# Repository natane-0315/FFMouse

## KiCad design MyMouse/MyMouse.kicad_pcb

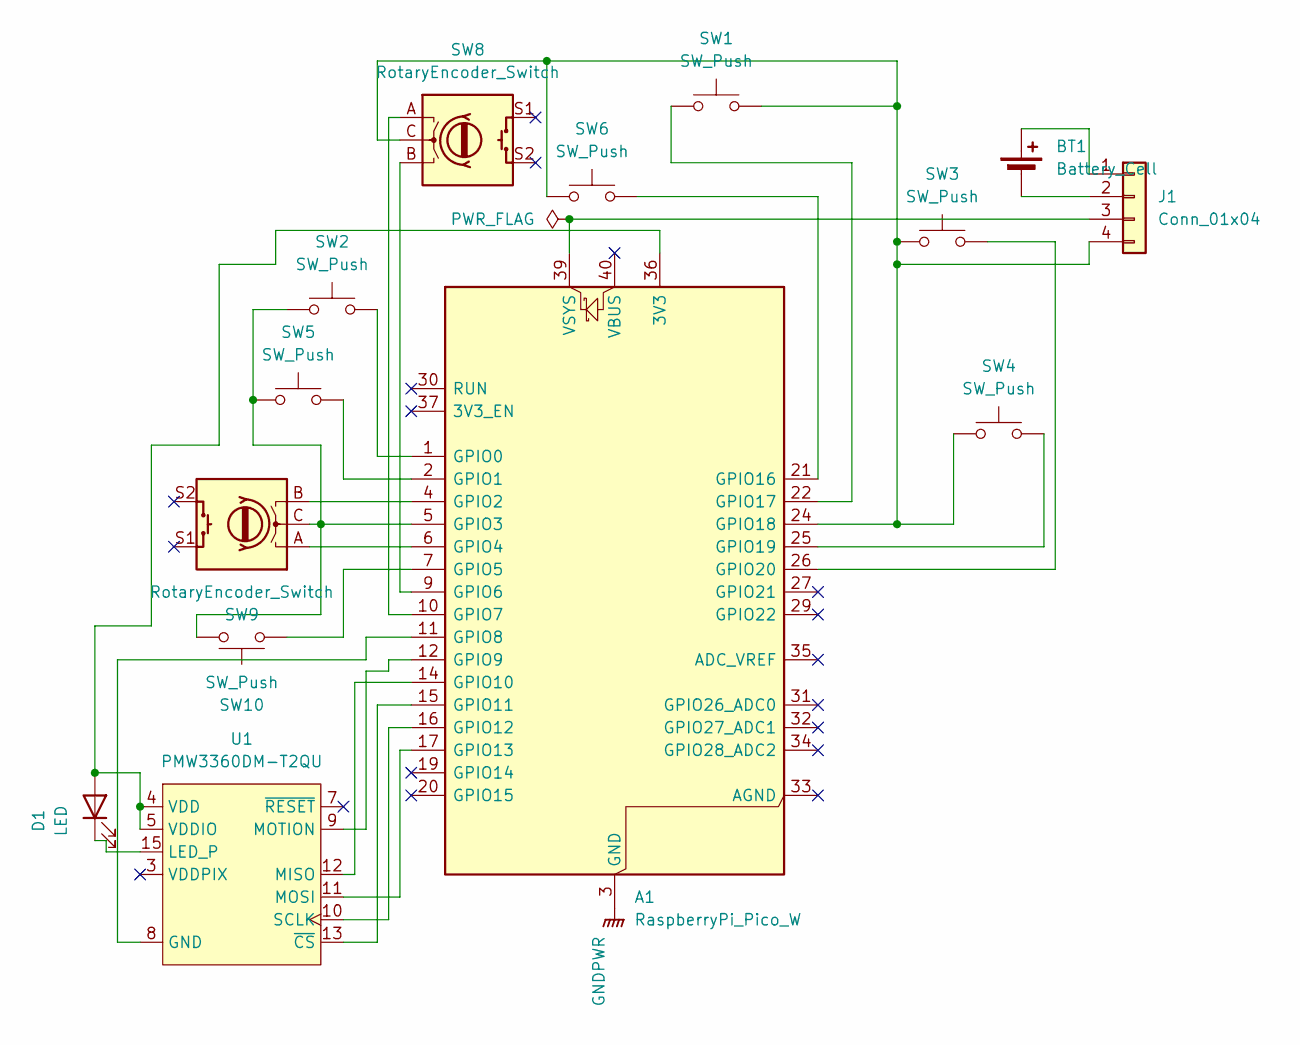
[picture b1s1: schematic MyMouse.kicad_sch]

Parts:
A1: RaspberryPi_Pico_W; RaspberryPi_Pico_W_SMD_HandSolder
BT1: Battery_Cell; PinHeader_1x04_P2.54mm_Vertical
D1: LED; JST_PH_B2B-PH-K_1x02_P2.00mm_Vertical
J1: Conn_01x04; PinHeader_1x04_P2.54mm_Vertical
SW1, SW2, SW3, SW4, SW5, SW6, SW10: SW_Push; SW_PUSH_6mm
SW8, SW9: RotaryEncoder_Switch; RotaryEncoder_Alps_EC11E-Switch_Vertical_H20mm
U1: PMW3360DM-T2QU; PMW3360DM-T2QU 16Pin

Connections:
GNDPWR: A1.3 (GND), A1.8 (GND), A1.13 (GND), A1.18 (GND), A1.23 (GND), A1.28 (GND), A1.38 (GND)
unnamed: A1.36 (3V3), D1.2 (A), U1.4 (VDD), U1.5 (VDDIO)
unnamed: A1.1 (GPIO0), SW2.2
unnamed: A1.2 (GPIO1), SW5.2
unnamed: A1.4 (GPIO2), SW9.B
unnamed: A1.5 (GPIO3), SW2.1, SW5.1, SW9.C, SW10.2
unnamed: A1.6 (GPIO4), SW9.A
unnamed: A1.7 (GPIO5), SW10.1
unnamed: A1.9 (GPIO6), SW8.B
unnamed: A1.10 (GPIO7), SW8.A
unnamed: A1.11 (GPIO8), U1.8 (GND)
unnamed: A1.12 (GPIO9), U1.9 (MOTION)
unnamed: A1.14 (GPIO10), U1.12 (MISO)
unnamed: A1.15 (GPIO11), U1.13 (~CS)
unnamed: A1.16 (GPIO12), U1.10 (SCLK)
unnamed: A1.17 (GPIO13), U1.11 (MOSI)
unnamed: A1.21 (GPIO16), SW6.2
unnamed: A1.22 (GPIO17), SW1.1
unnamed: A1.24 (GPIO18), J1.4, SW1.2, SW3.1, SW4.1, SW6.1, SW8.C
unnamed: A1.25 (GPIO19), SW4.2
unnamed: A1.26 (GPIO20), SW3.2
unnamed: A1.39 (VSYS), J1.3
unnamed: BT1.1 (+), J1.1
unnamed: BT1.2 (-), J1.2
unnamed: D1.1 (K), U1.15 (LED_P)

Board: 2 copper layers, 14 parts (0 on the bottom side), 25 nets, no tracks yet.

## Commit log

2026-01-26 adding Mouse project
2026-02-27 BlenderでShellを作った
2026-02-27 ファイル整理
